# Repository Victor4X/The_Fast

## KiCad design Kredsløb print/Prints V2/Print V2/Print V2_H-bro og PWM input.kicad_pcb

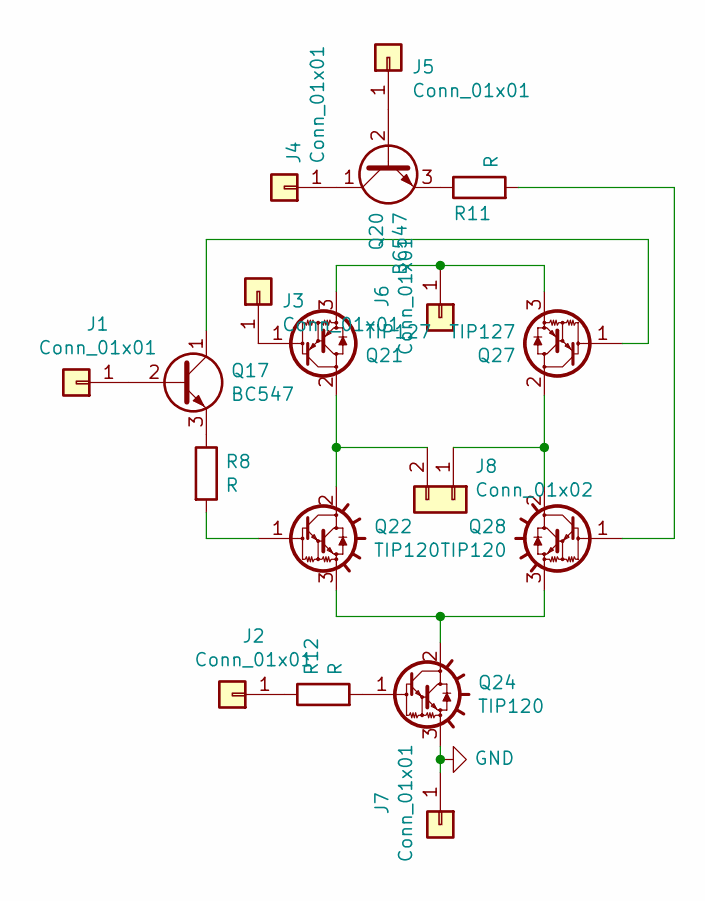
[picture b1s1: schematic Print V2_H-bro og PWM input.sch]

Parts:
J1, J2, J3, J4, J5, J6, J7: Conn_01x01; Wire_hole
J8: Conn_01x02; PinSocket_1x02_P2.54mm_Vertical
Q17, Q20: BC547; TO-92_Inline
Q21, Q27: TIP127; TO-220-3_Vertical
Q22, Q24, Q28: TIP120; TO-220-3_Vertical
R8, R11, R12: R; R_vandret

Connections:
GND: J7.1, Q24.3 (E)
unnamed: J1.1, Q17.2 (B)
unnamed: J2.1, R12.1
unnamed: J3.1, Q21.1 (B)
unnamed: J4.1, Q20.1 (C)
unnamed: J5.1, Q20.2 (B)
unnamed: J6.1, Q21.3 (E), Q27.3 (E)
unnamed: J8.1, Q27.2 (C), Q28.2 (C)
unnamed: J8.2, Q21.2 (C), Q22.2 (C)
unnamed: Q17.1 (C), Q27.1 (B)
unnamed: Q17.3 (E), R8.1
unnamed: Q20.3 (E), R11.1
unnamed: Q22.1 (B), R8.2
unnamed: Q22.3 (E), Q24.2 (C), Q28.3 (E)
unnamed: Q24.1 (B), R12.2
unnamed: Q28.1 (B), R11.2

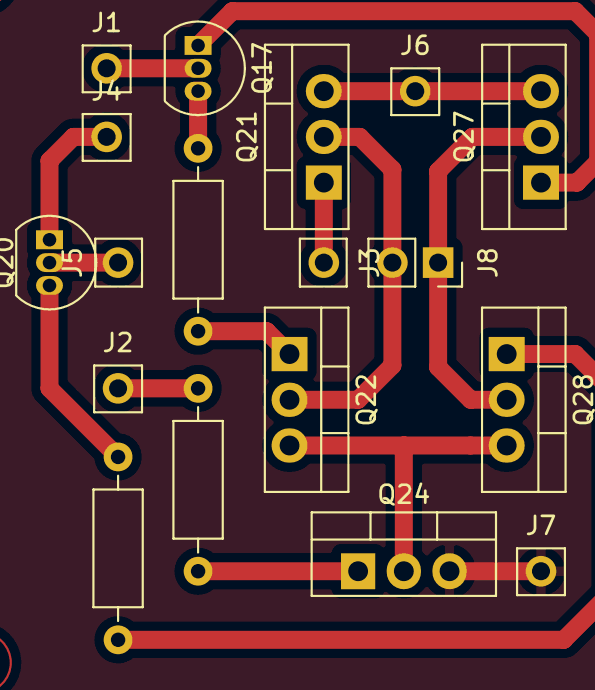
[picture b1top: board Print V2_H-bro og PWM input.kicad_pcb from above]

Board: 2 copper layers, 18 parts (0 on the bottom side), 16 nets.

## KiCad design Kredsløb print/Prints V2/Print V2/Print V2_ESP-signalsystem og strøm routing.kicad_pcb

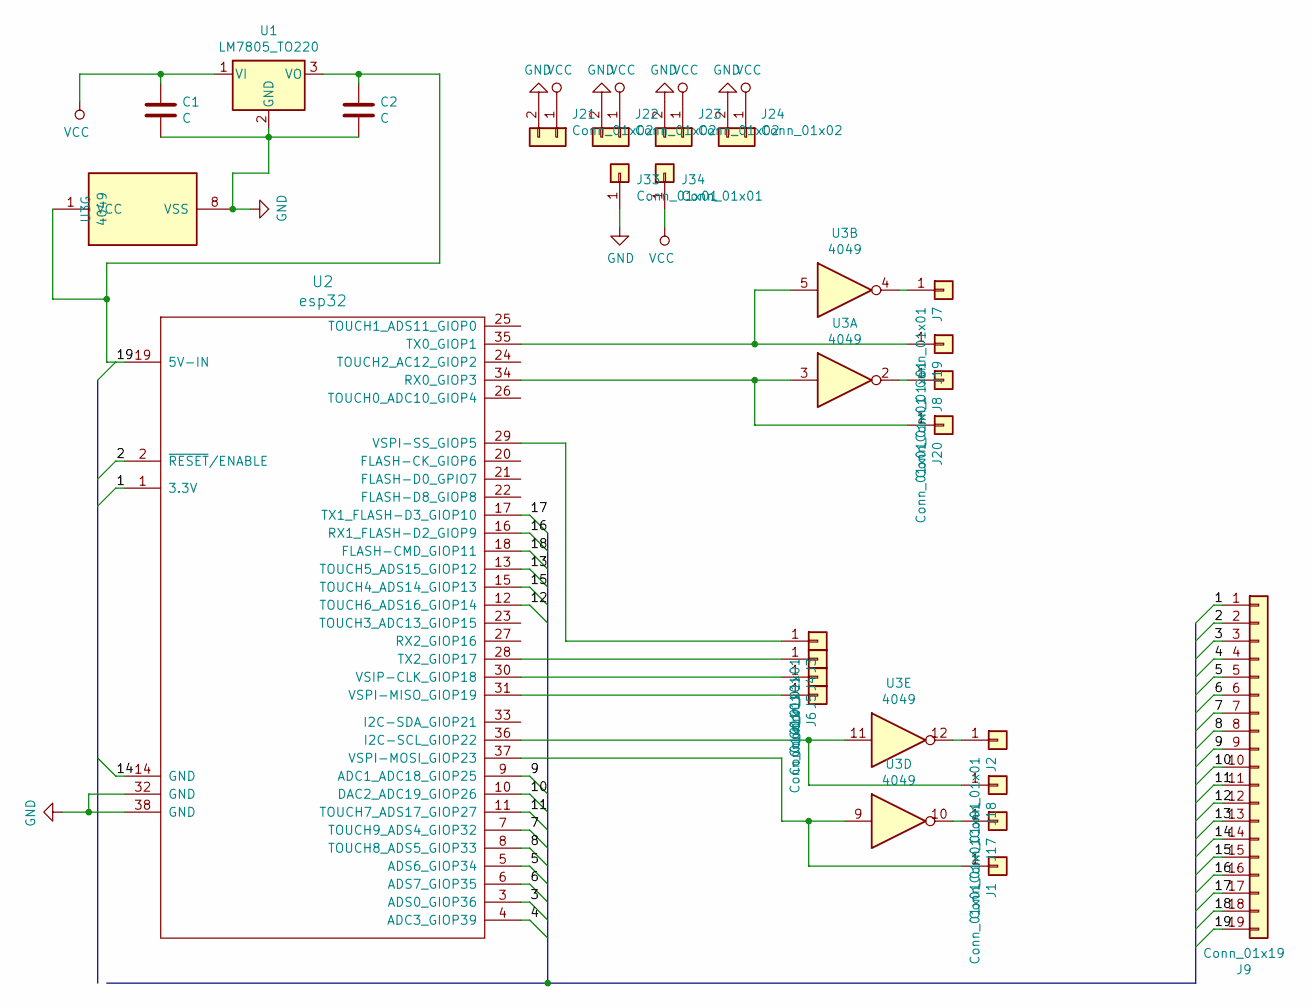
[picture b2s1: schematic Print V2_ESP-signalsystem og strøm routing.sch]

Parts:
C1, C2: C; C_6.00mm
J1, J2, J3, J4, J5, J6, J7, J8, J17, J18, J19, J20: Conn_01x01; PinSocket_1x01_P2.54mm_Vertical
J9: Conn_01x19; PinSocket_1x19_P2.54mm_Vertical
J21, J22, J23, J24: Conn_01x02; PinSocket_1x02_P2.54mm_Vertical
J33, J34: Conn_01x01; Power_wire_pad
U1: LM7805_TO220; TO-220-3_Vertical
U2: esp32; ESP32_mcu
U3: 4049; DIP-16_W7.62mm_LongPads

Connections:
/1: J9.1, U2.1 (3.3V)
/2: J9.2, U2.2 (~RESET~/ENABLE)
/3: J9.3, U2.3 (ADS0_GIOP36)
/4: J9.4, U2.4 (ADC3_GIOP39)
/5: J9.5, U2.5 (ADS6_GIOP34)
/6: J9.6, U2.6 (ADS7_GIOP35)
/7: J9.7, U2.7 (TOUCH9_ADS4_GIOP32)
/8: J9.8, U2.8 (TOUCH8_ADS5_GIOP33)
/9: J9.9, U2.9 (ADC1_ADC18_GIOP25)
/10: J9.10, U2.10 (DAC2_ADC19_GIOP26)
/11: J9.11, U2.11 (TOUCH7_ADS17_GIOP27)
/12: J9.12, U2.12 (TOUCH6_ADS16_GIOP14)
/13: J9.13, U2.13 (TOUCH5_ADS15_GIOP12)
/14: J9.14, U2.14 (GND)
/15: J9.15, U2.15 (TOUCH4_ADS14_GIOP13)
/16: J9.16, U2.16 (RX1_FLASH-D2_GIOP9)
/17: J9.17, U2.17 (TX1_FLASH-D3_GIOP10)
/18: J9.18, U2.18 (FLASH-CMD_GIOP11)
/19: C2.1, J9.19, U1.3 (VO), U2.19 (5V-IN), U3.1 (VCC)
GND: C1.2, C2.2, J21.2, J22.2, J23.2, J24.2, J33.1, U1.2 (GND), U2.32 (GND), U2.38 (GND), U3.8 (VSS)
unnamed: J1.1, U2.37 (VSPI-MOSI_GIOP23), U3.9
unnamed: J2.1, U3.12
unnamed: J3.1, U2.29 (VSPI-SS_GIOP5)
unnamed: J4.1, U2.28 (TX2_GIOP17)
unnamed: J5.1, U2.30 (VSIP-CLK_GIOP18)
unnamed: J6.1, U2.31 (VSPI-MISO_GIOP19)
unnamed: J7.1, U3.4
unnamed: J8.1, U3.2
unnamed: J17.1, U3.10
unnamed: J18.1, U2.36 (I2C-SCL_GIOP22), U3.11
unnamed: J19.1, U2.35 (TX0_GIOP1), U3.5
unnamed: J20.1, U2.34 (RX0_GIOP3), U3.3
VCC: C1.1, J21.1, J22.1, J23.1, J24.1, J34.1, U1.1 (VI)

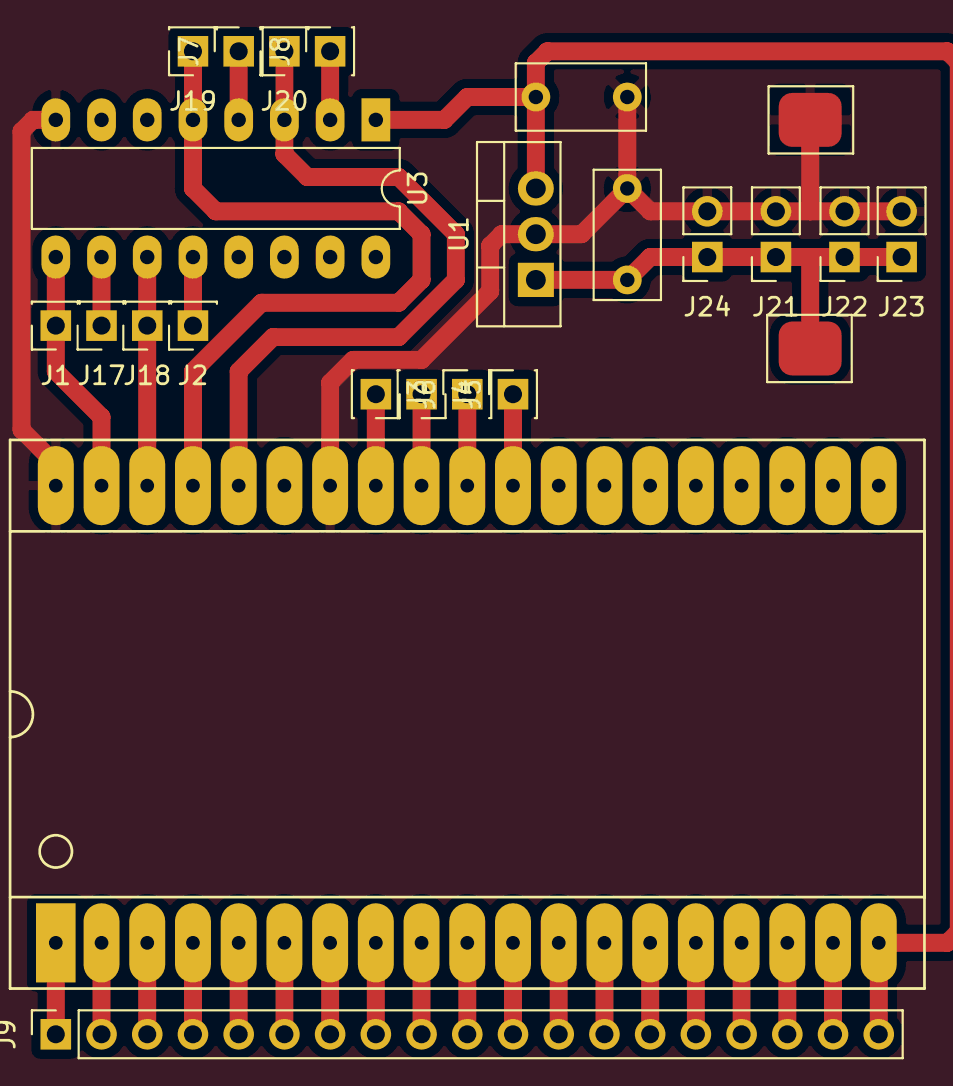
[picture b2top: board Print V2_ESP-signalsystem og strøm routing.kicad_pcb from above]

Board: 2 copper layers, 24 parts (0 on the bottom side), 33 nets.

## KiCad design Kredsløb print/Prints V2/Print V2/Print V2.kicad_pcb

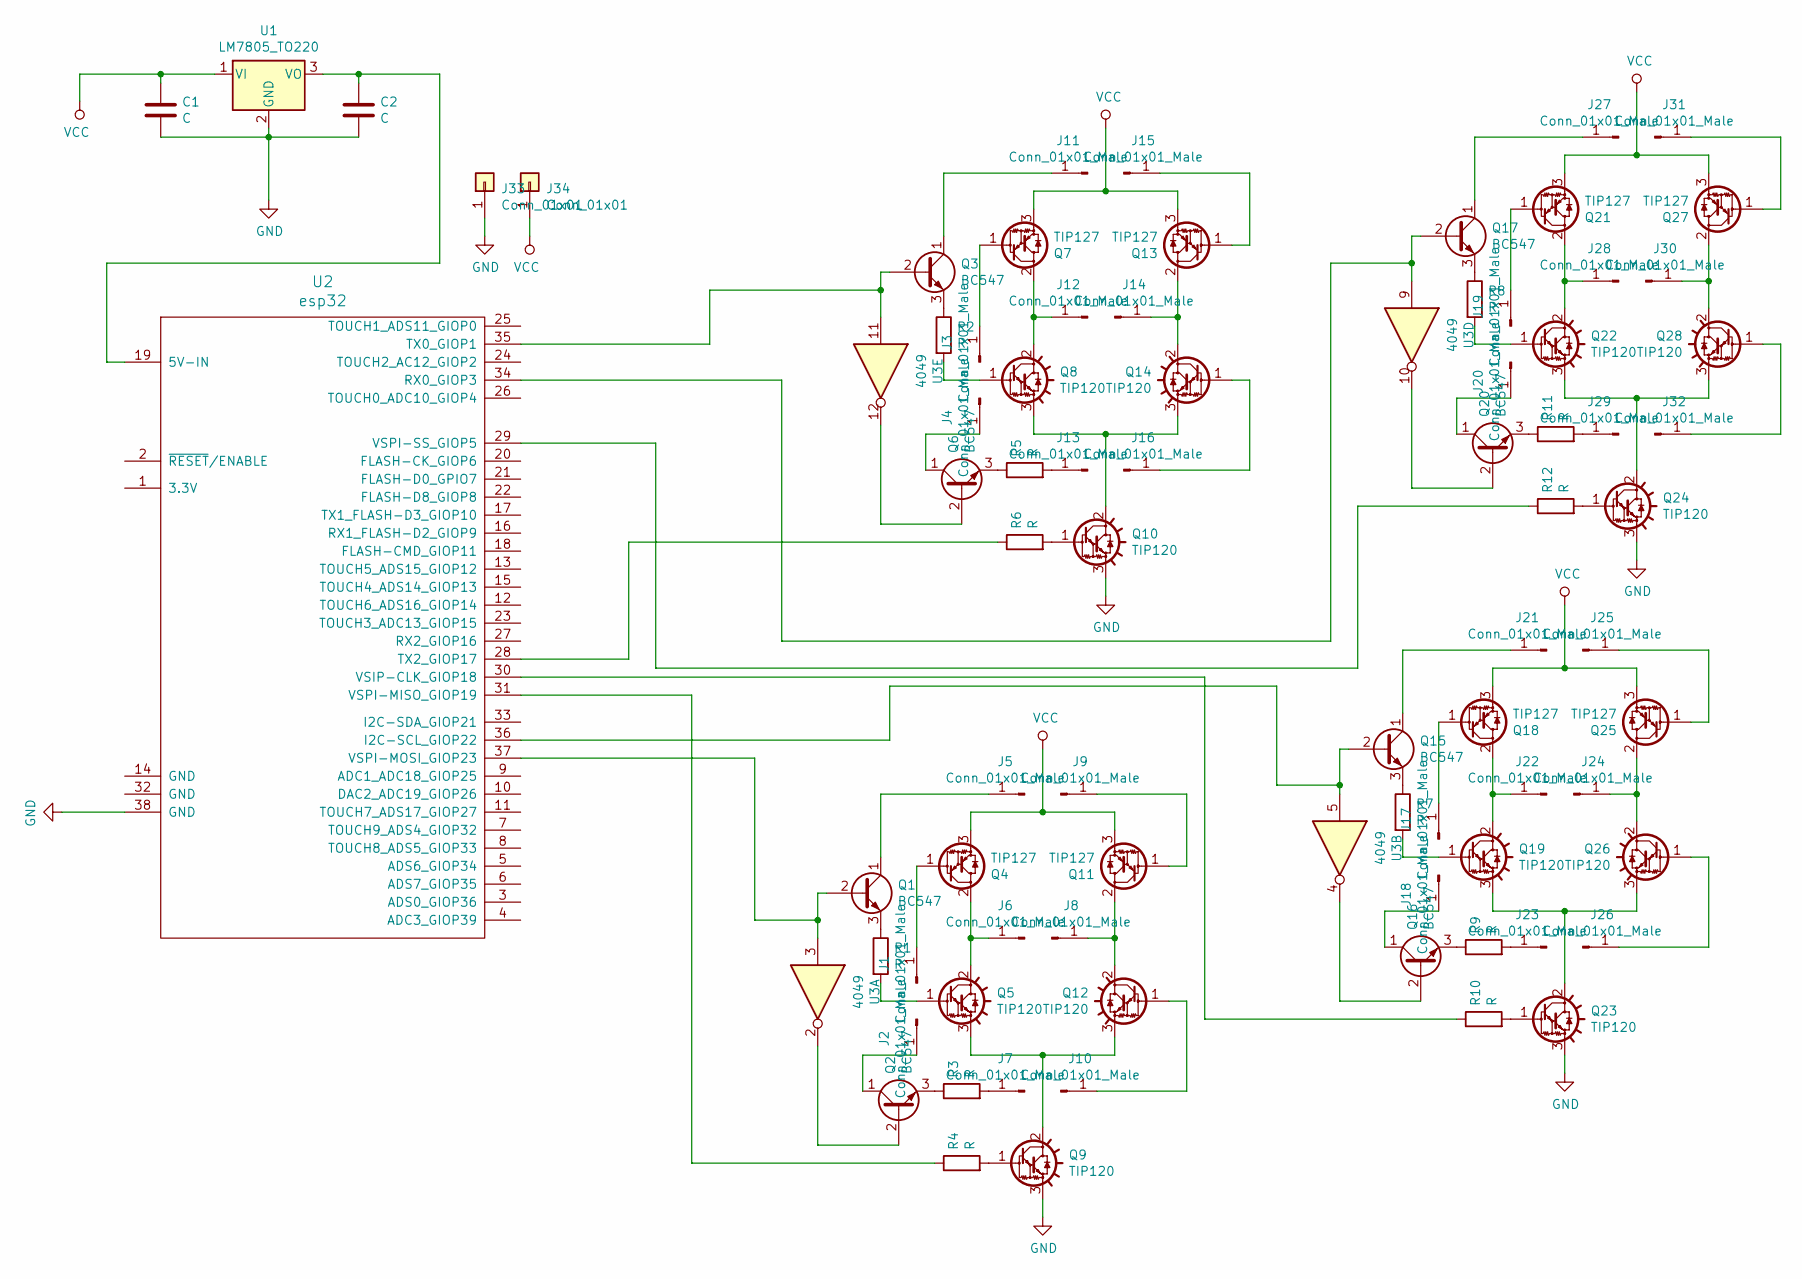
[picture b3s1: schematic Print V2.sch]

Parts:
C1, C2: C; C_6.00mm
J1, J2, J3, J4, J5, J6, J7, J8, J9, J10, J11, J12, J13, J14, J15, J16, J17, J18, J19, J20, J21, J22, J23, J24, J25, J26, J27, J28, J29, J30, J31, J32: Conn_01x01_Male; PinHeader_1x01_P1.00mm_Vertical
J33, J34: Conn_01x01; Power_wire_pad
Q1, Q2, Q3, Q6, Q15, Q16, Q17, Q20: BC547; TO-92_Inline
Q4, Q7, Q11, Q13, Q18, Q21, Q25, Q27: TIP127; TO-220-3_Vertical
Q5, Q8, Q9, Q10, Q12, Q14, Q19, Q22, Q23, Q24, Q26, Q28: TIP120; TO-220-3_Vertical
R1, R2, R3, R4, R5, R6, R7, R8, R9, R10, R11, R12: R; R_vandret
U1: LM7805_TO220; TO-220-3_Vertical
U2: esp32; ESP32_mcu
U3: 4049; DIP-16_W7.62mm_LongPads

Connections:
GND: C1.2, C2.2, J33.1, Q9.3 (E), Q10.3 (E), Q23.3 (E), Q24.3 (E), U1.2 (GND), U2.38 (GND), U3.8 (VSS)
unnamed: C2.1, U1.3 (VO), U2.19 (5V-IN), U3.1 (VCC)
unnamed: J1.1, Q4.1 (B)
unnamed: J2.1, Q2.1 (C)
unnamed: J3.1, Q7.1 (B)
unnamed: J4.1, Q6.1 (C)
unnamed: J5.1, Q1.1 (C)
unnamed: J6.1, Q4.2 (C), Q5.2 (C)
unnamed: J7.1, R3.2
unnamed: J8.1, Q11.2 (C), Q12.2 (C)
unnamed: J9.1, Q11.1 (B)
unnamed: J10.1, Q12.1 (B)
unnamed: J11.1, Q3.1 (C)
unnamed: J12.1, Q7.2 (C), Q8.2 (C)
unnamed: J13.1, R5.2
unnamed: J14.1, Q13.2 (C), Q14.2 (C)
unnamed: J15.1, Q13.1 (B)
unnamed: J16.1, Q14.1 (B)
unnamed: J17.1, Q18.1 (B)
unnamed: J18.1, Q16.1 (C)
unnamed: J19.1, Q21.1 (B)
unnamed: J20.1, Q20.1 (C)
unnamed: J21.1, Q15.1 (C)
unnamed: J22.1, Q18.2 (C), Q19.2 (C)
unnamed: J23.1, R9.2
unnamed: J24.1, Q25.2 (C), Q26.2 (C)
unnamed: J25.1, Q25.1 (B)
unnamed: J26.1, Q26.1 (B)
unnamed: J27.1, Q17.1 (C)
unnamed: J28.1, Q21.2 (C), Q22.2 (C)
unnamed: J29.1, R11.2
unnamed: J30.1, Q27.2 (C), Q28.2 (C)
unnamed: J31.1, Q27.1 (B)
unnamed: J32.1, Q28.1 (B)
unnamed: Q1.2 (B), U2.37 (VSPI-MOSI_GIOP23), U3.3
unnamed: Q1.3 (E), R1.1
unnamed: Q2.2 (B), U3.2
unnamed: Q2.3 (E), R3.1
unnamed: Q3.2 (B), U2.35 (TX0_GIOP1), U3.11
unnamed: Q3.3 (E), R2.1
unnamed: Q5.1 (B), R1.2
unnamed: Q6.2 (B), U3.12
unnamed: Q6.3 (E), R5.1
unnamed: Q8.1 (B), R2.2
unnamed: Q9.1 (B), R4.2
unnamed: Q10.1 (B), R6.2
unnamed: Q8.3 (E), Q10.2 (C), Q14.3 (E)
unnamed: Q5.3 (E), Q9.2 (C), Q12.3 (E)
unnamed: Q15.2 (B), U2.36 (I2C-SCL_GIOP22), U3.5
unnamed: Q15.3 (E), R7.1
unnamed: Q16.2 (B), U3.4
unnamed: Q16.3 (E), R9.1
unnamed: Q17.2 (B), U2.34 (RX0_GIOP3), U3.9
unnamed: Q17.3 (E), R8.1
unnamed: Q19.1 (B), R7.2
unnamed: Q19.3 (E), Q23.2 (C), Q26.3 (E)
unnamed: Q20.2 (B), U3.10
unnamed: Q20.3 (E), R11.1
unnamed: Q22.1 (B), R8.2
unnamed: Q22.3 (E), Q24.2 (C), Q28.3 (E)
unnamed: Q23.1 (B), R10.2
unnamed: Q24.1 (B), R12.2
unnamed: R4.1, U2.31 (VSPI-MISO_GIOP19)
unnamed: R6.1, U2.28 (TX2_GIOP17)
unnamed: R10.1, U2.30 (VSIP-CLK_GIOP18)
unnamed: R12.1, U2.29 (VSPI-SS_GIOP5)
VCC: C1.1, J34.1, Q4.3 (E), Q7.3 (E), Q11.3 (E), Q13.3 (E), Q18.3 (E), Q21.3 (E), Q25.3 (E), Q27.3 (E), U1.1 (VI)

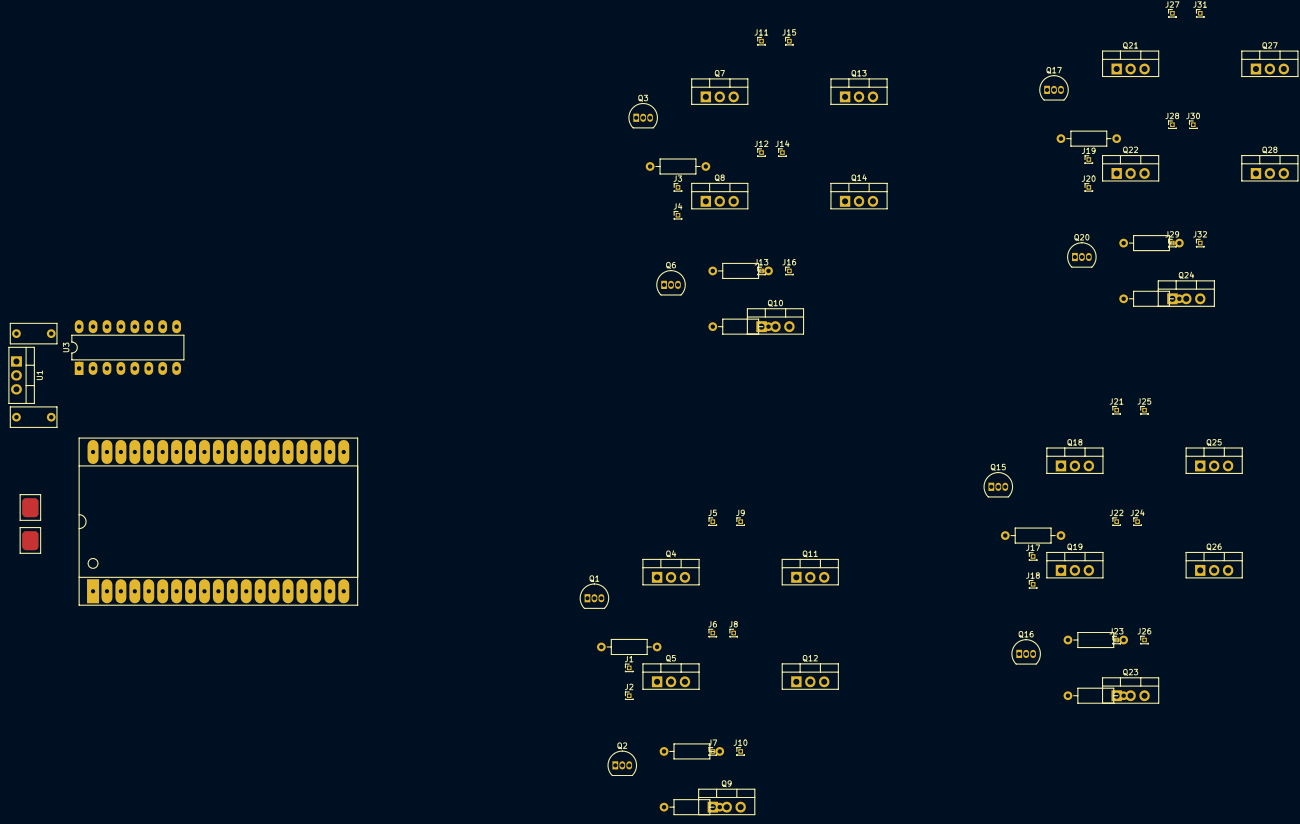
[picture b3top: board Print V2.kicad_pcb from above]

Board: 2 copper layers, 79 parts (0 on the bottom side), 67 nets.

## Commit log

2019-02-25 made a parser and stuff
2019-02-25 webserver done
2019-02-25 Interface with keyboard controls
2019-03-12 Design of robot parts
    Autocad-inventor
2019-03-15 Files - print
2019-03-15 refit and resize of print files
2019-03-15 Overgang fix (2.15)
2019-03-15 stuff
2019-03-15 more stuff
2019-03-18 new stuff
2019-03-18 newnew stuff
2019-03-18 even more stuff
2019-03-18 Multisim + one more for the bois
2019-03-18 again
2019-03-19 Updated Base part, new cutout needed
2019-03-20 base update
2019-03-20 fixed base
2019-03-20 nothing
2019-03-22 Base stuff
2019-03-22 not-gate added
2019-03-22 Flask og interface
2019-03-25 Interface updates (added turns)
2019-03-27 Kicad stuff + base update
2019-03-29 Parser finished
2019-03-29 lots of stuff (tested PWM)
2019-04-02 schematic and print update
2019-04-02 faktisk STL
2019-04-05 kredsløb og ny motor mount
2019-04-08 Lotsa stuff
2019-04-08 split
2019-04-09 New prints
2019-04-09 smol fix
2019-04-09 many fix
2019-04-09 ny overgang
2019-04-09 base stuff - pdf to cut
2019-04-09 big base
2019-04-09 Base fix
2019-04-10 V2!!
2019-04-10 V2.5!
2019-04-10 everything
2019-04-11 Documentation
2019-04-11 Base and mount to print
2019-04-11 new mount (fixed lenght)
2019-04-11 Combination
2019-04-11 Light thingy
2019-04-15 tdgdfg
2019-04-15 Find fem fejl
2019-04-15 FUCK SERIAL MONITOR
2019-04-16 done?
2019-04-25 Light stuff done
2019-04-28 More documents
2019-04-28 more
2019-04-28 Opdaterede Multisim diagrammer
2019-04-29 Last commit ppbly
2019-04-30 Or now...
